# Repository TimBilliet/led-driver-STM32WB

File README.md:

# 4 channel LED driver with STM32WB15CC
A RGBW led driver using SY7203 LED driver IC's that can be controlled via an external pwm signal or an STM32WB15CCU6.\
The input source is meant to be a 3S lipo battery.\
Designed for a school project in EAGLE 9.6.0. PCB's manufactured by JLCPCB. Components from LCSC.

## LED power:
P<sub>WHITE</sub> = 3V * 0,714A * 9 = 19,28W\
P<sub>RED</sub> = 2,15V * 0,14A * 8 = 2,41W\
P<sub>GREEN</sub> = 3,1V * 0,14A * 8 = 3,47W\
P<sub>BLUE</sub> = 3,1V * 0,14A * 8 = 3,47W\
P<sub>TOT</sub> = 19,28W + 2,41W + 3,47W + 3,47W = 28,63W

Because of this quite high power an aluminium PCB was used for the LED's. A heatsink and fan were attached to that PCB.

## Driver PCB

## LED PCB

## Mistakes
- Trying to use UART for programming the MCU.I was unable to get it working so i soldered wires to the ST-link pins to program it.
- Not using thermals on the copper pours. It's not a problem when using an oven but manual rework is a pain.
- Forgot to put via's to ground under the MCU. This has since been fixed.
- Using a MLPF-WB-02D3 RF filter on the antenna trace. I was unable to solder this, even in an oven. The pads were way too small for me.
- Using a reverse polarity protection MOSFET with a too low I<sub>D</sub>. When the battery was almost empty the current went up and the MOSFET got very hot.
- When testing the red LED's of the LED pcb i somehow blew them up. (red LED's have the lowest V<sub>f</sub> ....hmm)
- Not adding protection on the pwm pins. Any signal put on those pins goes straight to the MCU. I blew up an STM32 like this.

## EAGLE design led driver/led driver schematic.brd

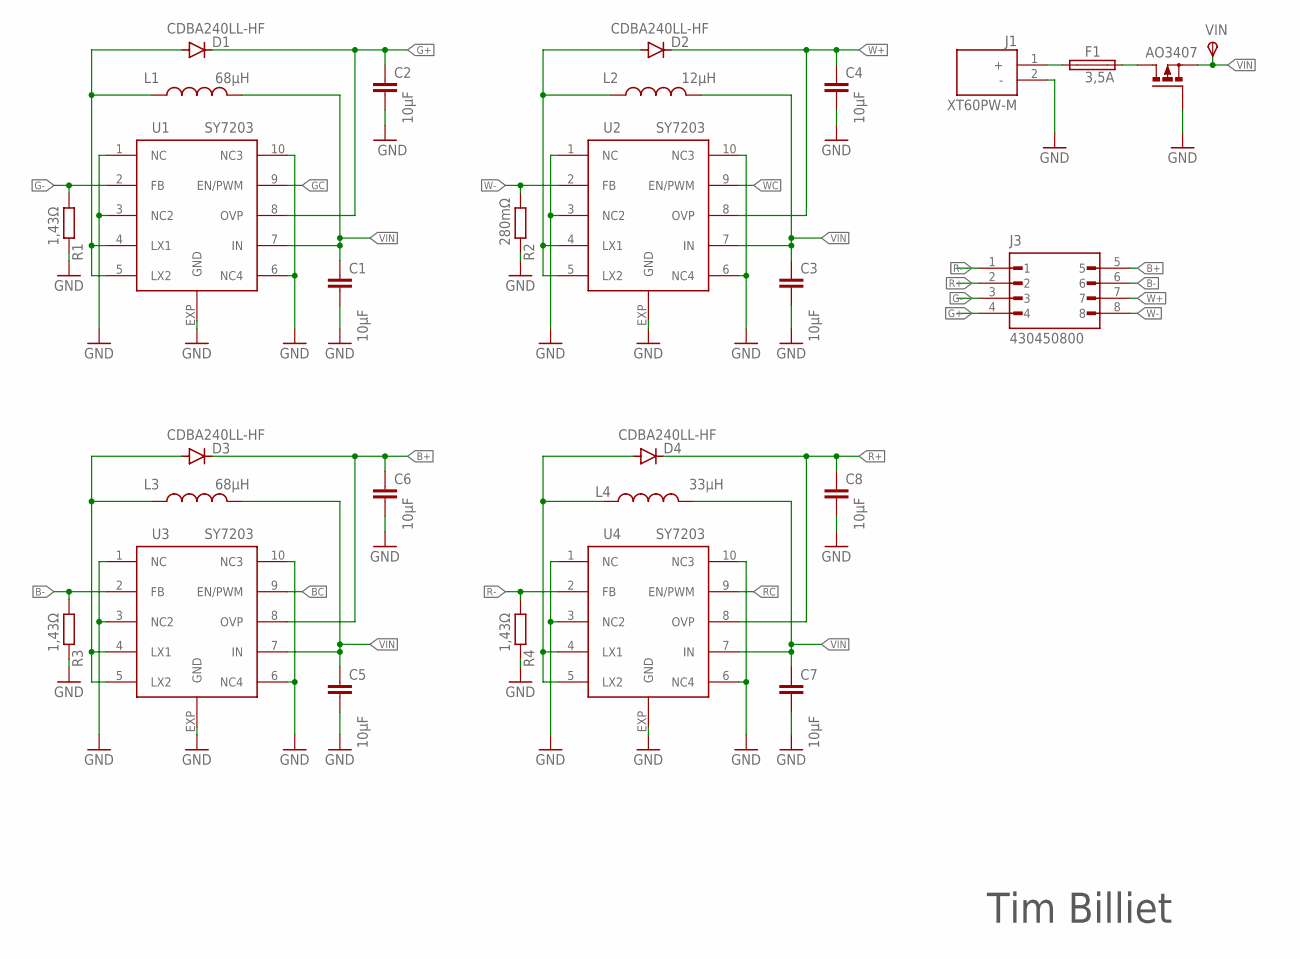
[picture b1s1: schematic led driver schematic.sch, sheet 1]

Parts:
C1, C2, C3, C4, C5, C6, C7, C8: 10µF; C0603
D1, D2, D3, D4: CDBA240LL-HF; DO-214AC
F1: 3,5A; R0603
J1: XT60PW-M; AMASS_XT60PW-M
J3: 430450800; MOLEX_430450800
L1, L3: 68µH; MBH125
L2: 12µH; MS127-120MT
L4: 33µH; MS127-120MT
Q1: AO3407; SOT23
R1, R3, R4: 1,43Ω; R0805
R2: 280mΩ; R0805
U1, U2, U3, U4: SY7203; DFN10-3X3
VIN: TPSTP10R; TP10R

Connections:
B+: C6.1, D3.C, J3.5, U3.8 (OVP)
B-: J3.6, R3.2, U3.2 (FB)
BC: U3.9 (EN/PWM); also elsewhere on the board
G+: C2.1, D1.C, J3.4, U1.8 (OVP)
G-: J3.3, R1.2, U1.2 (FB)
GC: U1.9 (EN/PWM); also elsewhere on the board
GND: C1.2, C2.2, C3.2, C4.2, C5.2, C6.2, C7.2, C8.2, J1.2 (-), Q1.1 (G), R1.1, R2.1, R3.1, R4.1, U1.1 (NC), U1.3 (NC2), U1.6 (NC4), U1.10 (NC3), U1.EXP (GND), U2.1 (NC), U2.3 (NC2), U2.6 (NC4), U2.10 (NC3), U2.EXP (GND), U3.1 (NC), U3.3 (NC2), U3.6 (NC4), U3.10 (NC3), U3.EXP (GND), U4.1 (NC), U4.3 (NC2), U4.6 (NC4), U4.10 (NC3), U4.EXP (GND); also elsewhere on the board
LX1: D1.A, L1.P$1 (1), U1.4 (LX1), U1.5 (LX2)
LX2: D2.A, L2.P$1 (1), U2.4 (LX1), U2.5 (LX2)
LX3: D3.A, L3.P$1 (1), U3.4 (LX1), U3.5 (LX2)
LX4: D4.A, L4.P$1 (1), U4.4 (LX1), U4.5 (LX2)
unnamed: F1.1, J1.1 (+)
unnamed: F1.2, Q1.3 (D)
R+: C8.1, D4.C, J3.2, U4.8 (OVP)
R-: J3.1, R4.2, U4.2 (FB)
RC: U4.9 (EN/PWM); also elsewhere on the board
VIN: C1.1, C3.1, C5.1, C7.1, L1.P$2 (2), L2.P$2 (2), L3.P$2 (2), L4.P$2 (2), Q1.2 (S), U1.7 (IN), U2.7 (IN), U3.7 (IN), U4.7 (IN), VIN.TP; also elsewhere on the board
W+: C4.1, D2.C, J3.7, U2.8 (OVP)
W-: J3.8, R2.2, U2.2 (FB)
WC: U2.9 (EN/PWM); also elsewhere on the board

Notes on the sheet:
Tim Billiet

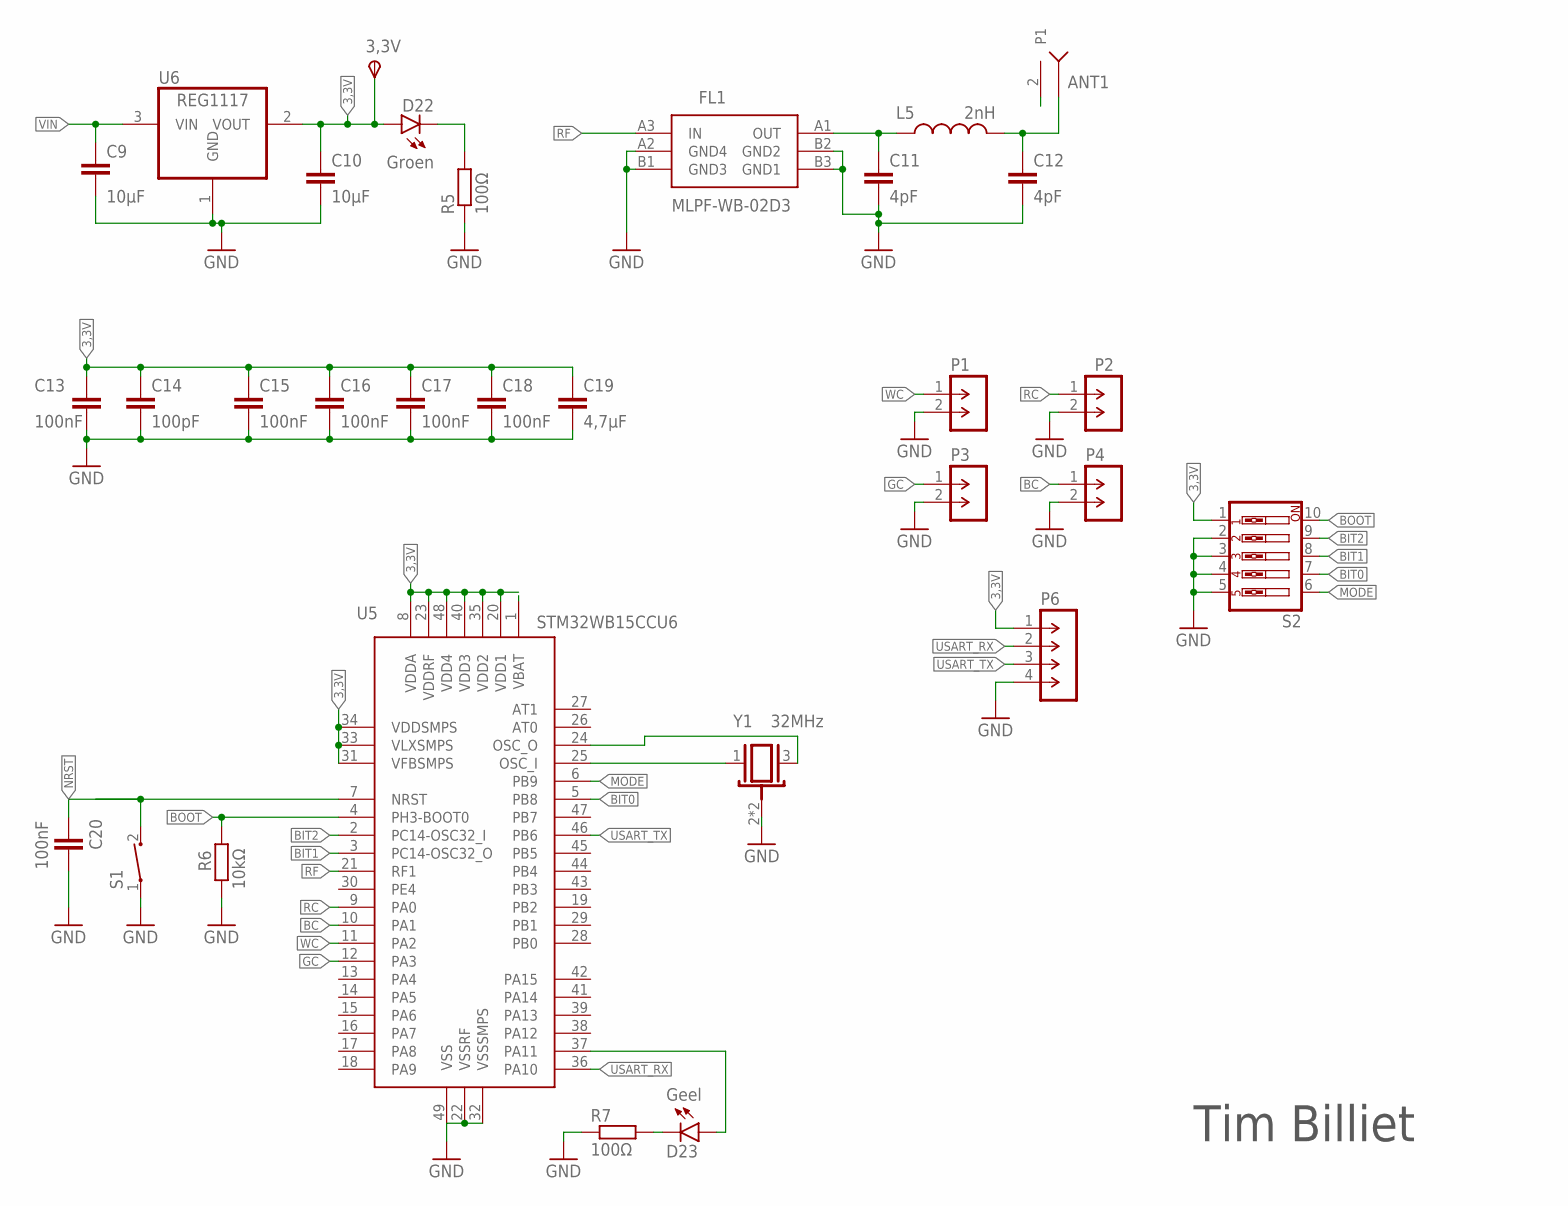
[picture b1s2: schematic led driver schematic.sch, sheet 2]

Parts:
3,3V: TPSTP10R; TP10R
ANT1: ANT3216LL00R2400A
C9, C10: 10µF; C0603
C11, C12: 4pF; C0603
C13, C15, C16, C17, C18, C20: 100nF; C0603
C14: 100pF; C0603
C19: 4,7µF; C0603
D22: Groen; CHIP-LED0603
D23: Geel; CHIP-LED0603
FL1: MLPF-WB-02D3; MLPFWB02D3
L5: 2nH; R0603
P1, P2, P3, P4: M-1X02-SIP-100-32; SIP-100-02-32
P6: M-1X04-SIP-100-32; SIP-100-04-32
R5, R7: 100Ω; R0603
R6: 10kΩ; R0603
S1: TS-1088R-02026; TS1088R02026
S2: SW_DIP-5; EDG-05
U5: STM32WB15CCU6; QFN50P700X700X60-49N
U6: REG1117; SOT223
Y1: 32MHz; OSC_NX2016SA

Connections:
3,3V: 3,3V.TP, C10.1, C13.1, C14.1, C15.1, C16.1, C17.1, C18.1, C19.1, D22.A, P6.1, S2.1, U5.1 (VBAT), U5.8 (VDDA), U5.20 (VDD1), U5.23 (VDDRF), U5.31 (VFBSMPS), U5.33 (VLXSMPS), U5.34 (VDDSMPS), U5.35 (VDD2), U5.40 (VDD3), U5.48 (VDD4), U6.2 (VOUT)
BC: P4.1, U5.10 (PA1); also elsewhere on the board
BIT0: S2.7, U5.5 (PB8)
BIT1: S2.8, U5.3 (PC14-OSC32_O)
BIT2: S2.9, U5.2 (PC14-OSC32_I)
BOOT: R6.2, S2.10, U5.4 (PH3-BOOT0)
GC: P3.1, U5.12 (PA3); also elsewhere on the board
GND: C9.2, C10.2, C11.2, C12.2, C13.2, C14.2, C15.2, C16.2, C17.2, C18.2, C19.2, C20.1, FL1.A2 (GND4), FL1.B1 (GND3), FL1.B2 (GND2), FL1.B3 (GND1), P1.2, P2.2, P3.2, P4.2, P6.4, R5.1, R6.1, R7.1, S1.1, S2.2, S2.3, S2.4, S2.5, U5.22 (VSSRF), U5.32 (VSSSMPS), U5.49 (VSS), U6.1 (GND), Y1.2 (GND), Y1.4 (GND); also elsewhere on the board
MODE: S2.6, U5.6 (PB9)
unnamed: ANT1.1 (ANTENNA), C12.1, L5.2
unnamed: D23.A, U5.37 (PA11)
unnamed: C11.1, FL1.A1 (OUT), L5.1
unnamed: U5.25 (OSC_I), Y1.1
unnamed: U5.24 (OSC_O), Y1.3
unnamed: D22.C, R5.2
unnamed: D23.C, R7.2
NRST: C20.2, S1.2, U5.7 (NRST)
RC: P2.1, U5.9 (PA0); also elsewhere on the board
RF: FL1.A3 (IN), U5.21 (RF1)
USART_RX: P6.2, U5.36 (PA10)
USART_TX: P6.3, U5.46 (PB6)
VIN: C9.1, U6.3 (VIN); also elsewhere on the board
WC: P1.1, U5.11 (PA2); also elsewhere on the board

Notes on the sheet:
Tim Billiet

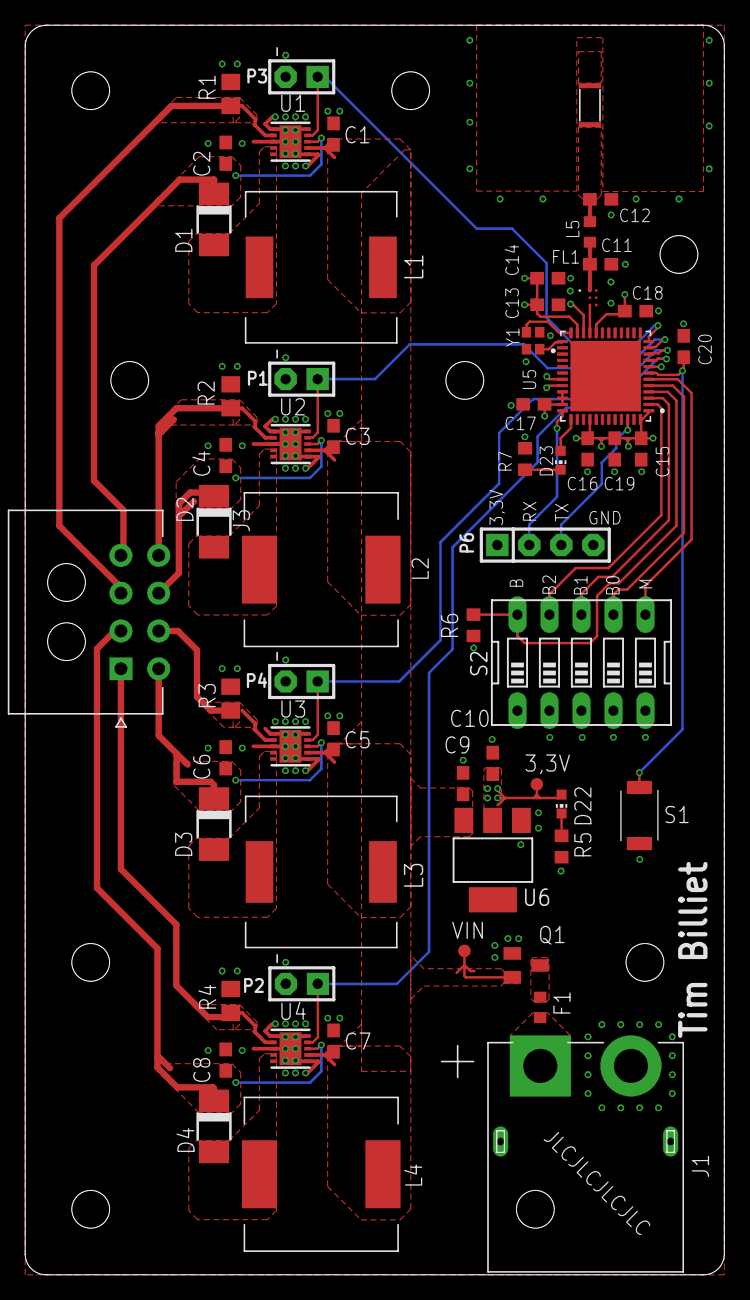
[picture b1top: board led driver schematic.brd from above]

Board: 4 copper layers, 55.5 x 99.2 mm, 60 parts (0 on the bottom side), 37 nets.

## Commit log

2024-04-29 added files

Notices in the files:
parts and their libraries:
con-headers-jp: Copyright (C) 2008, Bob Starr
